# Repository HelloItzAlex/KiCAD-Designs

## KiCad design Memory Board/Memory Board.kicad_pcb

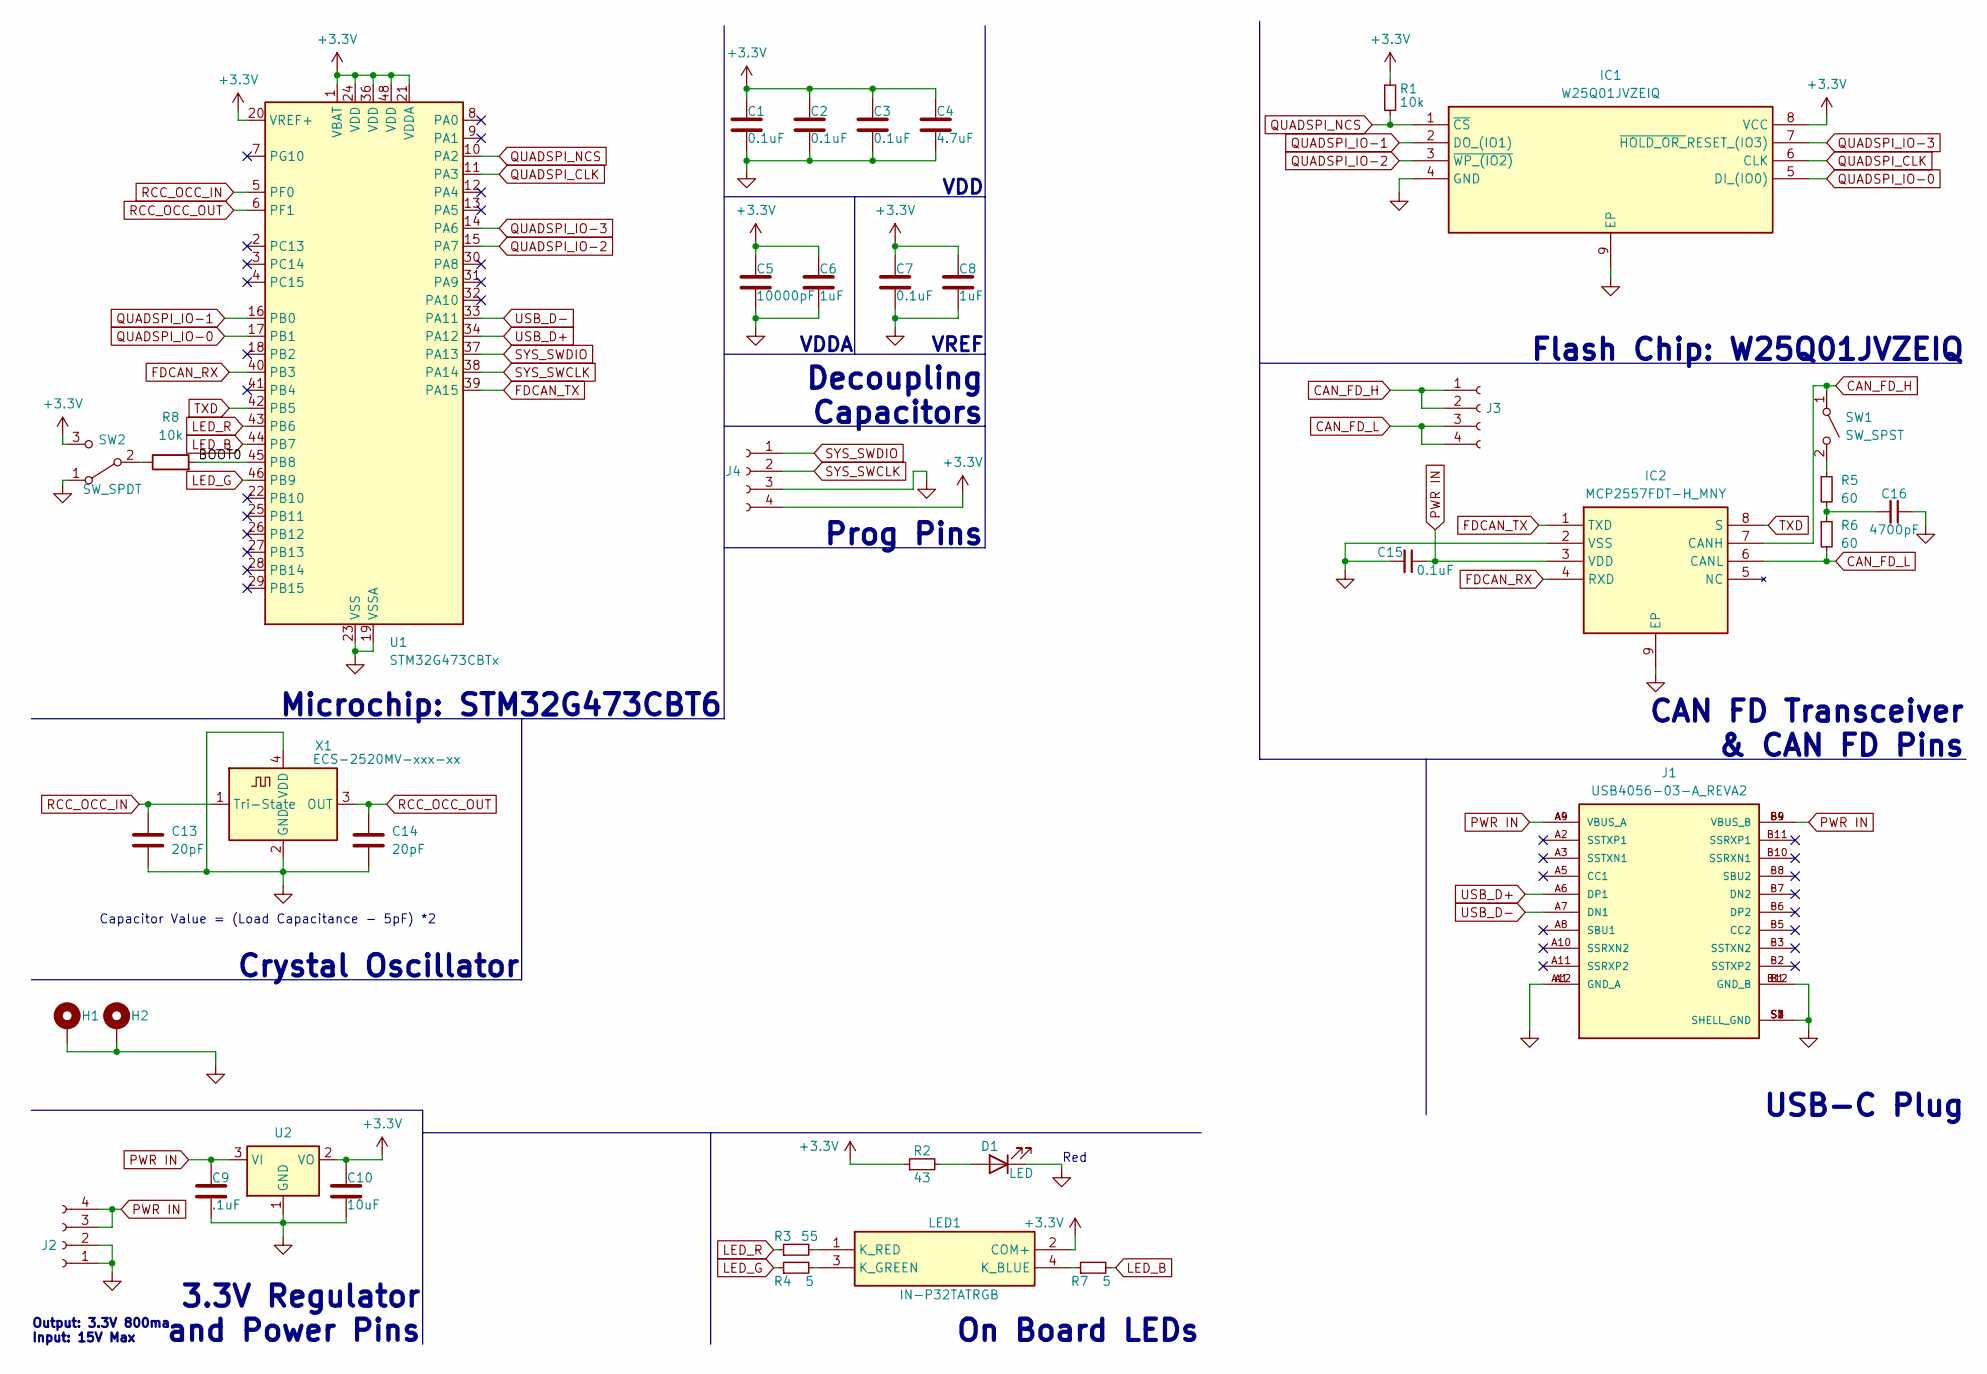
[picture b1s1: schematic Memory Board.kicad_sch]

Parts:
C1, C2, C3, C7, C15: 0.1uF; C_0402_1005Metric
C4: 4.7uF; C_0603_1608Metric
C5: 10000pF; C_0402_1005Metric
C6, C8: 1uF; C_0603_1608Metric
C9: .1uF; C_0402_1005Metric
C10: 10uF; C_0603_1608Metric
C13, C14: 20pF; C_0402_1005Metric
C16: 4700pF; C_0402_1005Metric
D1: LED; LED_0603_1608Metric
H1, H2: MountingHole_Pad; MountingHole_3.2mm_M3_Pad_TopBottom
IC1: W25Q01JVZEIQ; SON127P800X600X80-9N-D; Mouser Part Number 454-W25Q01JVZEIQ
IC2: MCP2557FDT-H_MNY; SON50P300X200X80-9N-D; Mouser Part Number 579-MCP2557FDT-H/MNY
J1: USB4056-03-A_REVA2; USB_C_Receptacle_GCT_USB4115-03-C; PARTREV A2
J2, J3, J4: Conn_01x04_Socket; PinHeader_1x04_P2.54mm_Vertical
LED1: IN-P32TATRGB; INP32TATRGB; Mouser Part Number 743-IN-P32TATRGB
R1: 10k; R_0603_1608Metric
R2: 43; R_0603_1608Metric
R3: 55; R_0402_1005Metric
R4, R7: 5; R_0402_1005Metric
R5, R6: 60; R_0805_2012Metric
R8: 10k; R_0402_1005Metric_Pad0.72x0.64mm_HandSolder
SW1: SW_SPST; SolderJumper-2_P1.3mm_Open_RoundedPad1.0x1.5mm
SW2: SW_SPDT; SolderJumper-3_P1.3mm_Open_RoundedPad1.0x1.5mm_NumberLabels
U1: STM32G473CBTx; LQFP-48_7x7mm_P0.5mm
U2: LD1117S33TR_SOT223; SOT-223-3_TabPin2
X1: ECS-2520MV-xxx-xx; Oscillator_SMD_ECS_2520MV-xxx-xx-4Pin_2.5x2.0mm

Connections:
+3.3V: C1.1, C2.1, C3.1, C4.1, C5.1, C6.1, C7.1, C8.1, C10.1, IC1.8 (VCC), J4.4, LED1.2 (COM+), R1.1, R2.1, SW2.3 (C), U1.1 (VBAT), U1.20 (VREF+), U1.21 (VDDA), U1.24 (VDD), U1.36 (VDD), U1.48 (VDD), U2.2 (VO); also elsewhere on the board
/BOOT0: R8.2, U1.45 (PB8)
CAN_FD_H: IC2.7 (CANH), J3.1, J3.2, SW1.1 (A)
CAN_FD_L: IC2.6 (CANL), J3.3, J3.4, R6.2
FDCAN_RX: IC2.4 (RXD), U1.40 (PB3)
FDCAN_TX: IC2.1 (TXD), U1.39 (PA15)
GND: C1.2, C2.2, C3.2, C4.2, C5.2, C6.2, C7.2, C8.2, C9.2, C10.2, C13.2, C14.2, C15.2, C16.1, D1.1 (K), H1.1, H2.1, IC1.4 (GND), IC1.9 (EP), IC2.2 (VSS), IC2.9 (EP), J1.A1 (GND_A), J1.A12 (GND_A), J1.B1 (GND_B), J1.B12 (GND_B), J1.S1 (SHELL_GND), J1.S2 (SHELL_GND), J1.S3 (SHELL_GND), J1.S4 (SHELL_GND), J2.1, J2.2, J4.3, SW2.1 (A), U1.19 (VSSA), U1.23 (VSS), U1.35 (VSS), U1.47 (VSS), U2.1 (GND), X1.2 (GND), X1.4 (VDD); also elsewhere on the board
LED_B: R7.2, U1.44 (PB7)
LED_G: R4.1, U1.46 (PB9)
LED_R: R3.1, U1.43 (PB6)
unnamed: C16.2, R5.2, R6.1
unnamed: D1.2 (A), R2.2
unnamed: LED1.4 (K_BLUE), R7.1
unnamed: LED1.3 (K_GREEN), R4.2
unnamed: LED1.1 (K_RED), R3.2
unnamed: R5.1, SW1.2 (B)
unnamed: R8.1, SW2.2 (B)
PWR IN: C9.1, C15.1, IC2.3 (VDD), J1.A4 (VBUS_A), J1.A9 (VBUS_A), J1.B4 (VBUS_B), J1.B9 (VBUS_B), J2.3, J2.4, U2.3 (VI)
QUADSPI_CLK: IC1.6 (CLK), U1.11 (PA3); also elsewhere on the board
QUADSPI_IO-0: IC1.5 (DI_(IO0)), U1.17 (PB1); also elsewhere on the board
QUADSPI_IO-1: IC1.2 (DO_(IO1)), U1.16 (PB0); also elsewhere on the board
QUADSPI_IO-2: IC1.3 (~WP_(IO2)), U1.15 (PA7); also elsewhere on the board
QUADSPI_IO-3: IC1.7 (~HOLD_OR_RESET_(IO3)), U1.14 (PA6); also elsewhere on the board
QUADSPI_NCS: IC1.1 (~CS), R1.2, U1.10 (PA2); also elsewhere on the board
RCC_OCC_IN: C13.1, U1.5 (PF0), X1.1 (Tri-State)
RCC_OCC_OUT: C14.1, U1.6 (PF1), X1.3 (OUT)
SYS_SWCLK: J4.2, U1.38 (PA14)
SYS_SWDIO: J4.1, U1.37 (PA13)
TXD: IC2.8 (S), U1.42 (PB5)
USB_D+: J1.A6 (DP1), U1.34 (PA12)
USB_D-: J1.A7 (DN1), U1.33 (PA11)

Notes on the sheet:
Capacitor Value = (Load Capacitance - 5pF) *2
Microchip: STM32G473CBT6
3.3V Regulator and Power Pins
USB-C Plug
Flash Chip: W25Q01JVZEIQ
Crystal Oscillator
On Board LEDs
Output: 3.3V 800ma Input: 15V Max
Red
VDD
CAN FD Transceiver & CAN FD Pins
Decoupling Capacitors
VREF
Prog Pins
VDDA

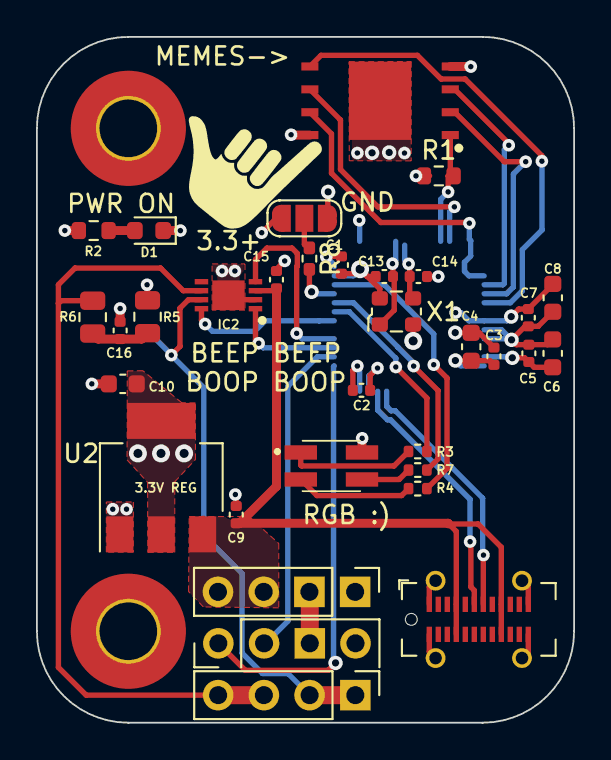
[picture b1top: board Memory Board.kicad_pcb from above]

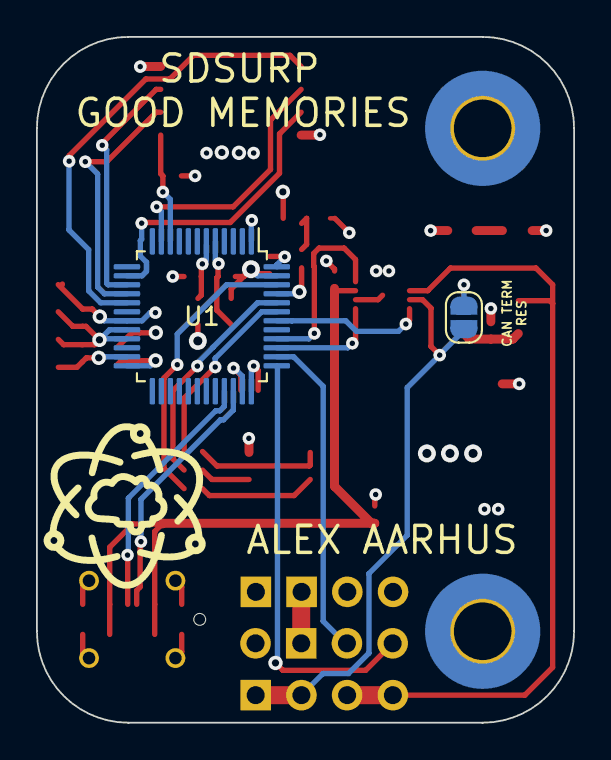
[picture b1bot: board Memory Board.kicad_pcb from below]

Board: 4 copper layers, 29.8 x 38.1 mm, 37 parts (2 on the bottom side), 31 nets.

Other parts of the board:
MEMES->: W25Q01JVZEIQ; SON127P800X600X80-9N-D

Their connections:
+3.3V: MEMES->.8 (VCC); also elsewhere on the board
GND: MEMES->.4 (GND), MEMES->.9 (EP); also elsewhere on the board
QUADSPI_CLK: MEMES->.6 (CLK); also elsewhere on the board
QUADSPI_IO-0: MEMES->.5 (DI_(IO0)); also elsewhere on the board
QUADSPI_IO-1: MEMES->.2 (DO_(IO1)); also elsewhere on the board
QUADSPI_IO-2: MEMES->.3 (~WP_(IO2)); also elsewhere on the board
QUADSPI_IO-3: MEMES->.7 (~HOLD_OR_RESET_(IO3)); also elsewhere on the board
QUADSPI_NCS: MEMES->.1 (~CS); also elsewhere on the board

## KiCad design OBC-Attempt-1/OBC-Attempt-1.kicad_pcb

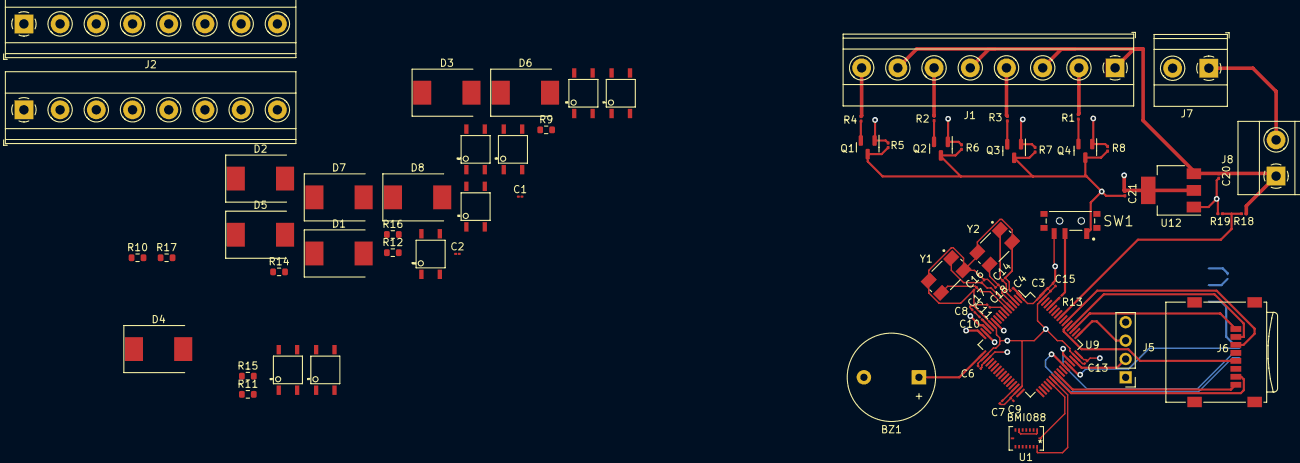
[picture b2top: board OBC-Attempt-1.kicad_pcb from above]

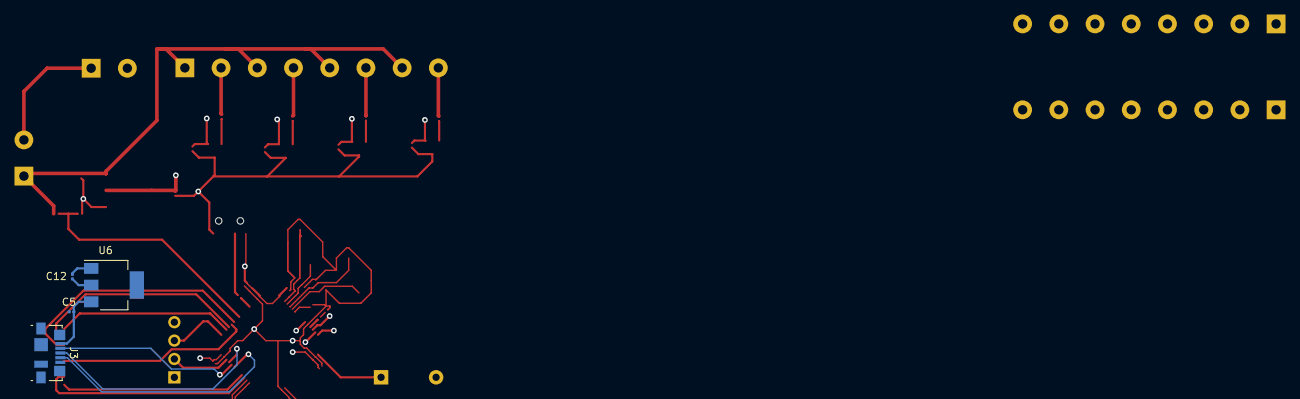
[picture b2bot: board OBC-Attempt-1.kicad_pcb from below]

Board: 4 copper layers, 75 parts (4 on the bottom side), 72 nets.

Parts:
BZ1: Buzzer; Buzzer_12x9.5RM7.6
C1, C2, C3, C4, C6, C8, C9, C11, C13: 100nF; C_01005_0402Metric
C5, C20: 100nF; C_0201_0603Metric
C7, C15: 4.7uF; C_01005_0402Metric
C10: 1uF; C_01005_0402Metric
C12, C21: 10uF; C_0201_0603Metric
C14, C16: 26pf; C_01005_0402Metric
C17, C18: 26uf; C_01005_0402Metric
D1, D2, D3, D4, D5, D6, D7, D8: B330; D_SMC
J1, J2, J4: Screw_Terminal_01x08; TerminalBlock_Phoenix_MKDS-1,5-8_1x08_P5.00mm_Horizontal
J3: USB_B_Micro; USB_Micro-B_Molex_47346-0001
J5: Conn_01x04; PinHeader_1x04_P2.54mm_Vertical
J6: Micro_SD_Card; microSD_HC_Wuerth_693072010801
J7, J8: Screw_Terminal_01x02; TerminalBlock_Phoenix_MKDS-1,5-2_1x02_P5.00mm_Horizontal
Q1, Q2, Q3, Q4: 2N7002K; SOT-23
R1, R2, R3, R4: 1; R_0201_0603Metric
R5, R6, R7, R8: 470; R_0201_0603Metric
R9, R10, R11, R12, R14, R15, R16, R17: 270; R_0603_1608Metric
R13: 10k; R_01005_0402Metric
R18: 1M; R_0201_0603Metric
R19: 100K; R_0201_0603Metric
SW1: PCM12SMTR; SW_PCM12SMTR
U1: BMI088
U2, U3, U4, U5, U7, U8, U10, U11: CPC1020NTR; 4-SOP
U6, U12: NCP1117-3.3_SOT223; SOT-223-3_TabPin2
U9: STM32F401RDTx; LQFP-64_10x10mm_P0.5mm
Y1: ABMM2-25MHZ-D1-T; XTAL_ABMM2-25.000MHZ-D1-T
Y2: ABMM2-32.768MHZ-E2F-T; XTAL_ABMM2-32.768MHZ-E2F-T

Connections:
3.3V: C1.1, C2.1, C3.1, C4.1, C6.1, C9.1, C10.1, C12.1, C13.1, C15.2, C21.1, J5.1, J6.4 (VDD), SW1.3, U1.3 (VDD), U1.11 (VDDIO), U6.2 (VO), U9.1 (VBAT), U9.13 (VREF+), U9.19 (VDD), U9.32 (VDD), U9.48 (VDD), U9.64 (VDD), U12.2 (VO)
BATT+: J7.1, J8.2
BUZZER: BZ1.1 (-), U9.17 (PA3)
CS1_ACC: U1.14 (CSB1), U9.25 (PC5)
CS2_GYRO: U1.5 (CSB2), U9.24 (PC4)
GND: BZ1.2 (+), C1.2, C2.2, C3.2, C4.2, C5.2, C6.2, C7.2, C8.2, C9.2, C11.2, C12.2, C13.2, C14.2, C15.1, C16.2, C17.2, C18.2, C20.2, C21.2, D1.2 (A), D2.2 (A), D3.2 (A), D4.2 (A), D5.2 (A), D6.2 (A), D7.2 (A), D8.2 (A), J2.1, J2.3, J2.5, J2.7, J3.5 (GND), J4.1, J4.3, J4.5, J4.7, J5.4, J6.6 (VSS), J7.2, Q1.3 (D), Q2.3 (D), Q3.3 (D), Q4.3 (D), R5.1, R6.1, R7.1, R8.1, R19.2, SW1.1, U1.2 (NC), U1.4 (GNDA), U1.6 (GNDIO), U1.7 (PS), U2.2, U3.2, U4.2, U5.2, U6.1 (GND), U7.2, U8.2, U9.12 (VSSA), U9.18 (VSS), U9.31 (VSS), U9.47 (VSS), U9.63 (VSS), U10.2, U11.2, U12.1 (GND), Y1.2 (GND), Y1.4 (GND), Y2.2 (GND), Y2.4 (GND)
INT_ACC1: U1.16 (INT1), U9.37 (PC6)
INT_ACC2: U1.1 (INT2), U9.38 (PC7)
INT_GYRO1: U1.12 (INT3), U9.41 (PA8)
INT_GYRO2: U1.13 (INT4), U9.42 (PA9)
MISO: U1.10 (SDO2), U1.15 (SDO1), U9.22 (PA6)
MOSI: U1.9 (SDA/SDI), U9.23 (PA7)
unnamed: C5.1, J3.1 (VBUS), U6.3 (VI)
unnamed: C7.1, U9.30 (VCAP1)
unnamed: C8.1, C10.2
unnamed: C11.1, U9.7 (NRST)
unnamed: D1.1 (K), J2.2, U4.4
unnamed: D2.1 (K), J2.8, U5.4
unnamed: D3.1 (K), J2.4, U2.4
unnamed: D4.1 (K), J2.6, U3.4
unnamed: D5.1 (K), J4.4, U10.4
unnamed: D6.1 (K), J4.6, U11.4
unnamed: D7.1 (K), J4.2, U7.4
unnamed: D8.1 (K), J4.8, U8.4
unnamed: J1.2, R1.2
unnamed: J1.4, R3.2
unnamed: J1.6, R2.2
unnamed: J1.8, R4.2
unnamed: Q1.2 (S), R4.1
unnamed: Q2.2 (S), R2.1
unnamed: Q3.2 (S), R3.1
unnamed: Q4.2 (S), R1.1
unnamed: R9.1, U2.1
unnamed: R10.1, U3.1
unnamed: R11.1, U4.1
unnamed: R12.1, U5.1
unnamed: R13.1, U9.60 (BOOT0)
unnamed: R13.2, SW1.2
unnamed: R14.1, U7.1
unnamed: R15.1, U8.1
unnamed: R16.1, U10.1
unnamed: R17.1, U11.1
PWR: C20.1, J1.1, J1.3, J1.5, J1.7, J8.1, R18.1, U2.3, U3.3, U4.3, U5.3, U7.3, U8.3, U10.3, U11.3, U12.3 (VI)
PYRO1: Q4.1 (G), R8.2, U9.11 (PC3)
PYRO2: Q3.1 (G), R7.2, U9.14 (PA0)
PYRO3: Q2.1 (G), R6.2, U9.15 (PA1)
PYRO4: Q1.1 (G), R5.2, U9.16 (PA2)
RCC_OSC32_IN: C14.1, U9.3 (PC14), Y2.1
RCC_OSC32_OUT: C18.1, U9.4 (PC15), Y2.3
RCC_OSC_IN: C16.1, U9.5 (PH0), Y1.1
RCC_OSC_OUT: C17.1, U9.6 (PH1), Y1.3
SCK: U1.8 (SCL/SCK), U9.21 (PA5)
SDIO_CK: J6.5 (CLK), U9.53 (PC12)
SDIO_CMD: J6.3 (CMD), U9.54 (PD2)
SDIO_D0: J6.7 (DAT0), U9.39 (PC8)
SDIO_D1: J6.8 (DAT1), U9.40 (PC9)
SDIO_D2: J6.1 (DAT2), U9.51 (PC10)
SDIO_D3: J6.2 (DAT3/CD), U9.52 (PC11)
SOL1: R11.2, U9.26 (PB0)
SOL2: R9.2, U9.27 (PB1)
SOL3: R10.2, U9.28 (PB2)
SOL4: R12.2, U9.29 (PB10)
SOL5: R14.2, U9.33 (PB12)
SOL6: R16.2, U9.34 (PB13)
SOL7: R17.2, U9.35 (PB14)
SOL8: R15.2, U9.36 (PB15)
SYS_JTCK_SWCLK: J5.3, U9.49 (PA14)
SYS_JTMS-SWDIO: J5.2, U9.46 (PA13)
USB_OTG_FS_DM: J3.2 (D-), U9.44 (PA11)
USB_OTG_FS_DP: J3.3 (D+), U9.45 (PA12)
USB_OTG_FS_ID: J3.4 (ID), U9.43 (PA10)
VMON: R18.2, R19.1, U9.56 (PB4)

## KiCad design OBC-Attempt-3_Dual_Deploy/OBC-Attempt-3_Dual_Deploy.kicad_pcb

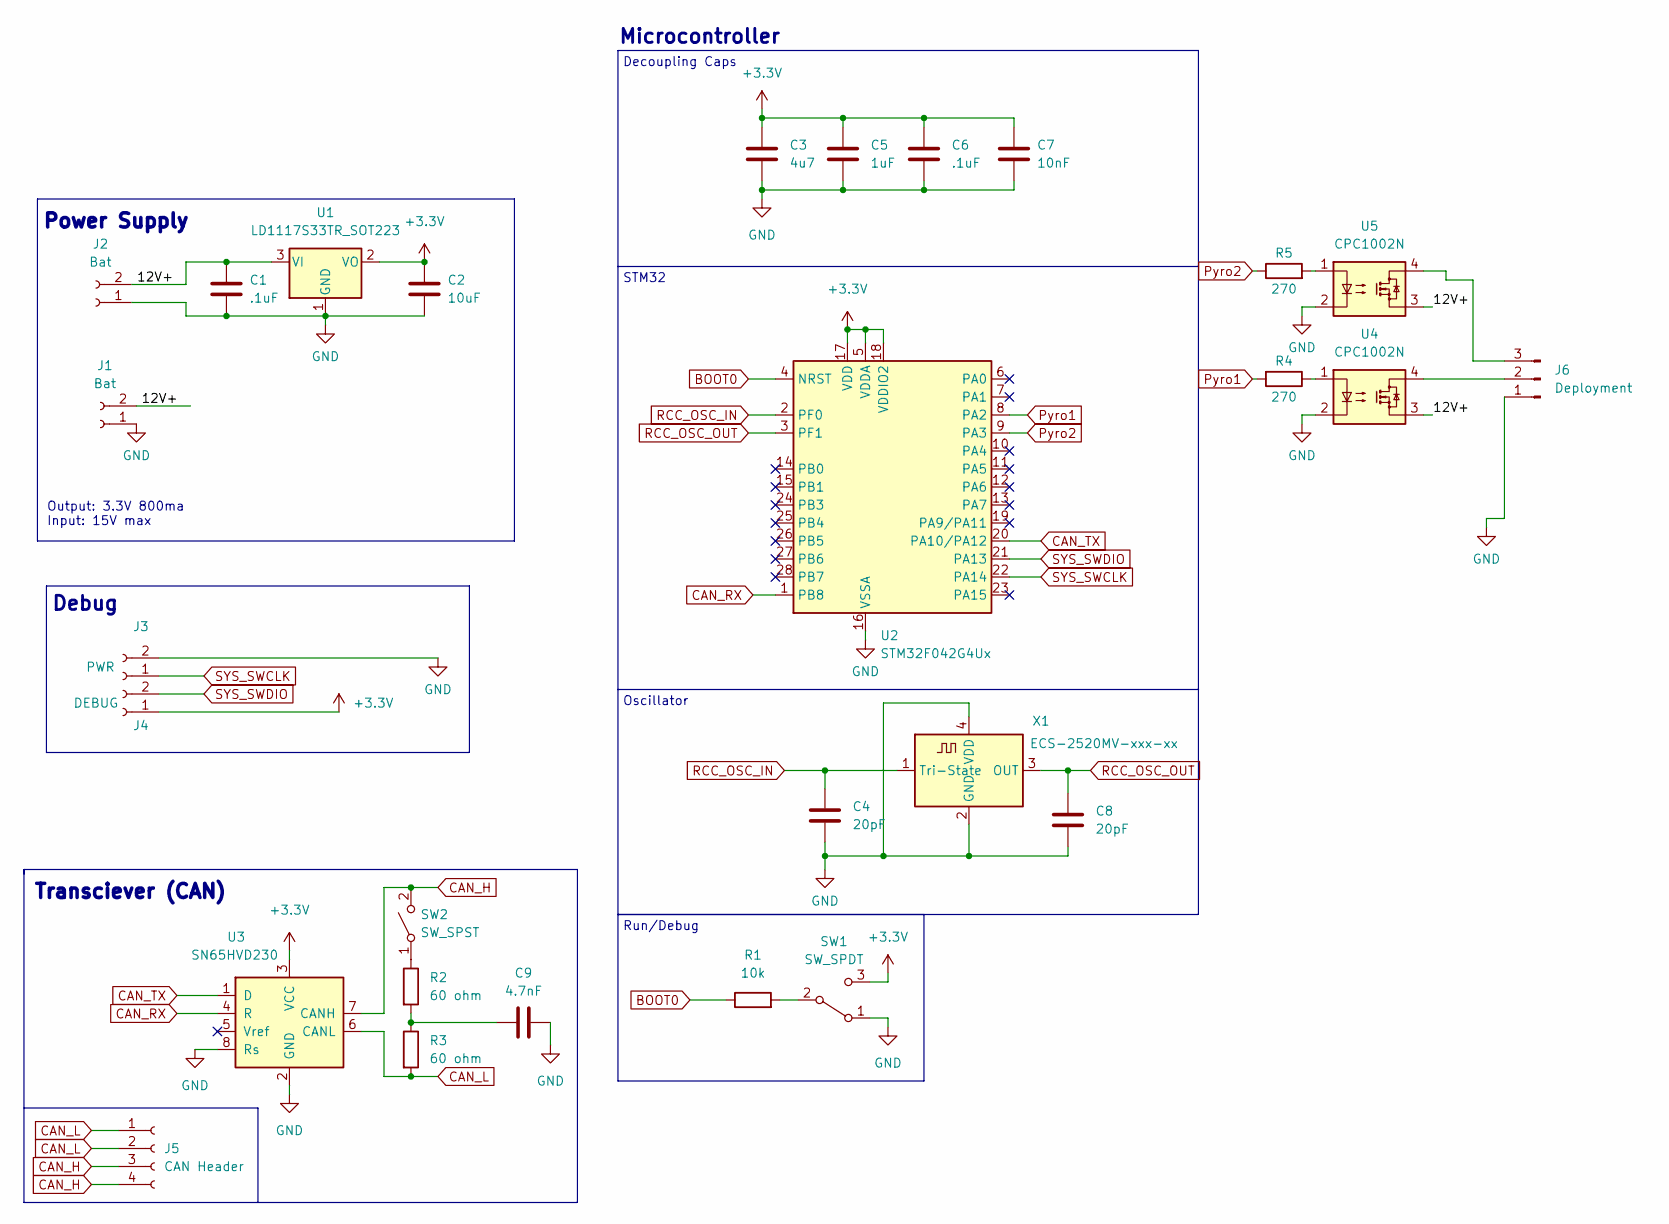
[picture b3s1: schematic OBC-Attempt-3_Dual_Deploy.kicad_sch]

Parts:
C1, C6: .1uF; C_0402_1005Metric
C2: 10uF; C_0603_1608Metric
C3: 4u7; C_0402_1005Metric
C4, C8: 20pF; C_0402_1005Metric
C5: 1uF; C_0402_1005Metric
C7: 10nF; C_0402_1005Metric
C9: 4.7nF; C_0402_1005Metric
J1, J2: Bat; PinHeader_1x02_P1.00mm_Vertical
J3: PWR; PinHeader_1x02_P1.00mm_Vertical
J4: DEBUG; PinHeader_1x02_P1.00mm_Vertical
J5: CAN Header; PinHeader_1x04_P1.00mm_Vertical
J6: Deployment; PinSocket_1x03_P2.54mm_Vertical
R1: 10k; R_0402_1005Metric
R2, R3: 60 ohm; R_0805_2012Metric
R4, R5: 270; R_0402_1005Metric
SW1: SW_SPDT; SolderJumper-3_P1.3mm_Open_RoundedPad1.0x1.5mm_NumberLabels
SW2: SW_SPST; SolderJumper-2_P1.3mm_Open_RoundedPad1.0x1.5mm
U1: LD1117S33TR_SOT223; SOT-223-3_TabPin2
U2: STM32F042G4Ux; QFN-28_4x4mm_P0.5mm
U3: SN65HVD230; SOIC-8_3.9x4.9mm_P1.27mm
U4, U5: CPC1002N; SOP-4_3.8x4.1mm_P2.54mm
X1: ECS-2520MV-xxx-xx; Oscillator_SMD_ECS_2520MV-xxx-xx-4Pin_2.5x2.0mm

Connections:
+3.3V: C2.1, C3.1, C5.1, C6.1, C7.1, J4.1, SW1.3 (C), U1.2 (VO), U2.5 (VDDA), U2.17 (VDD), U2.18 (VDDIO2), U3.3 (VCC)
/12V+: C1.1, J1.2, J2.2, U1.3 (VI), U4.3, U5.3
BOOT0: R1.1, U2.4 (NRST)
CAN_H: J5.3, J5.4, SW2.2 (B), U3.7 (CANH)
CAN_L: J5.1, J5.2, R3.2, U3.6 (CANL)
CAN_RX: U2.1 (PB8), U3.4 (R)
CAN_TX: U2.20 (PA10/PA12), U3.1 (D)
GND: C1.2, C2.2, C3.2, C4.2, C5.2, C6.2, C7.2, C8.2, C9.2, J1.1, J2.1, J3.2, J6.1, SW1.1 (A), U1.1 (GND), U2.16 (VSSA), U3.2 (GND), U3.8 (Rs), U4.2, U5.2, X1.2 (GND), X1.4 (VDD)
unnamed: C9.1, R2.2, R3.1
unnamed: R1.2, SW1.2 (B)
unnamed: R2.1, SW2.1 (A)
unnamed: R4.1, U4.1
unnamed: R5.2, U5.1
unnamed: J6.2, U4.4
unnamed: J6.3, U5.4
Pyro1: R4.2, U2.8 (PA2)
Pyro2: R5.1, U2.9 (PA3)
RCC_OSC_IN: C4.1, U2.2 (PF0), X1.1 (Tri-State)
RCC_OSC_OUT: C8.1, U2.3 (PF1), X1.3 (OUT)
SYS_SWCLK: J3.1, U2.22 (PA14)
SYS_SWDIO: J4.2, U2.21 (PA13)

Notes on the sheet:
Debug
Microcontroller
Output: 3.3V 800ma Input: 15V max
Oscillator
Run/Debug
Power Supply
Decoupling Caps
Transciever (CAN)
STM32

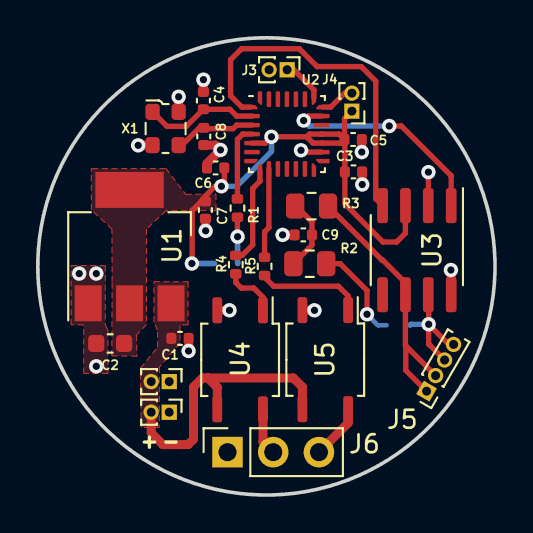
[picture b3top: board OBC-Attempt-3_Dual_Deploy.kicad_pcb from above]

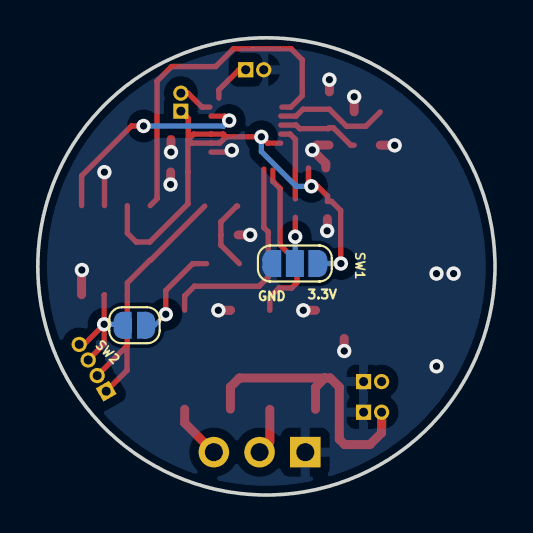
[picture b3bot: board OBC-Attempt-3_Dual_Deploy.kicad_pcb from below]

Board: 2 copper layers, 25.4 x 25.4 mm, 28 parts (2 on the bottom side), 21 nets.

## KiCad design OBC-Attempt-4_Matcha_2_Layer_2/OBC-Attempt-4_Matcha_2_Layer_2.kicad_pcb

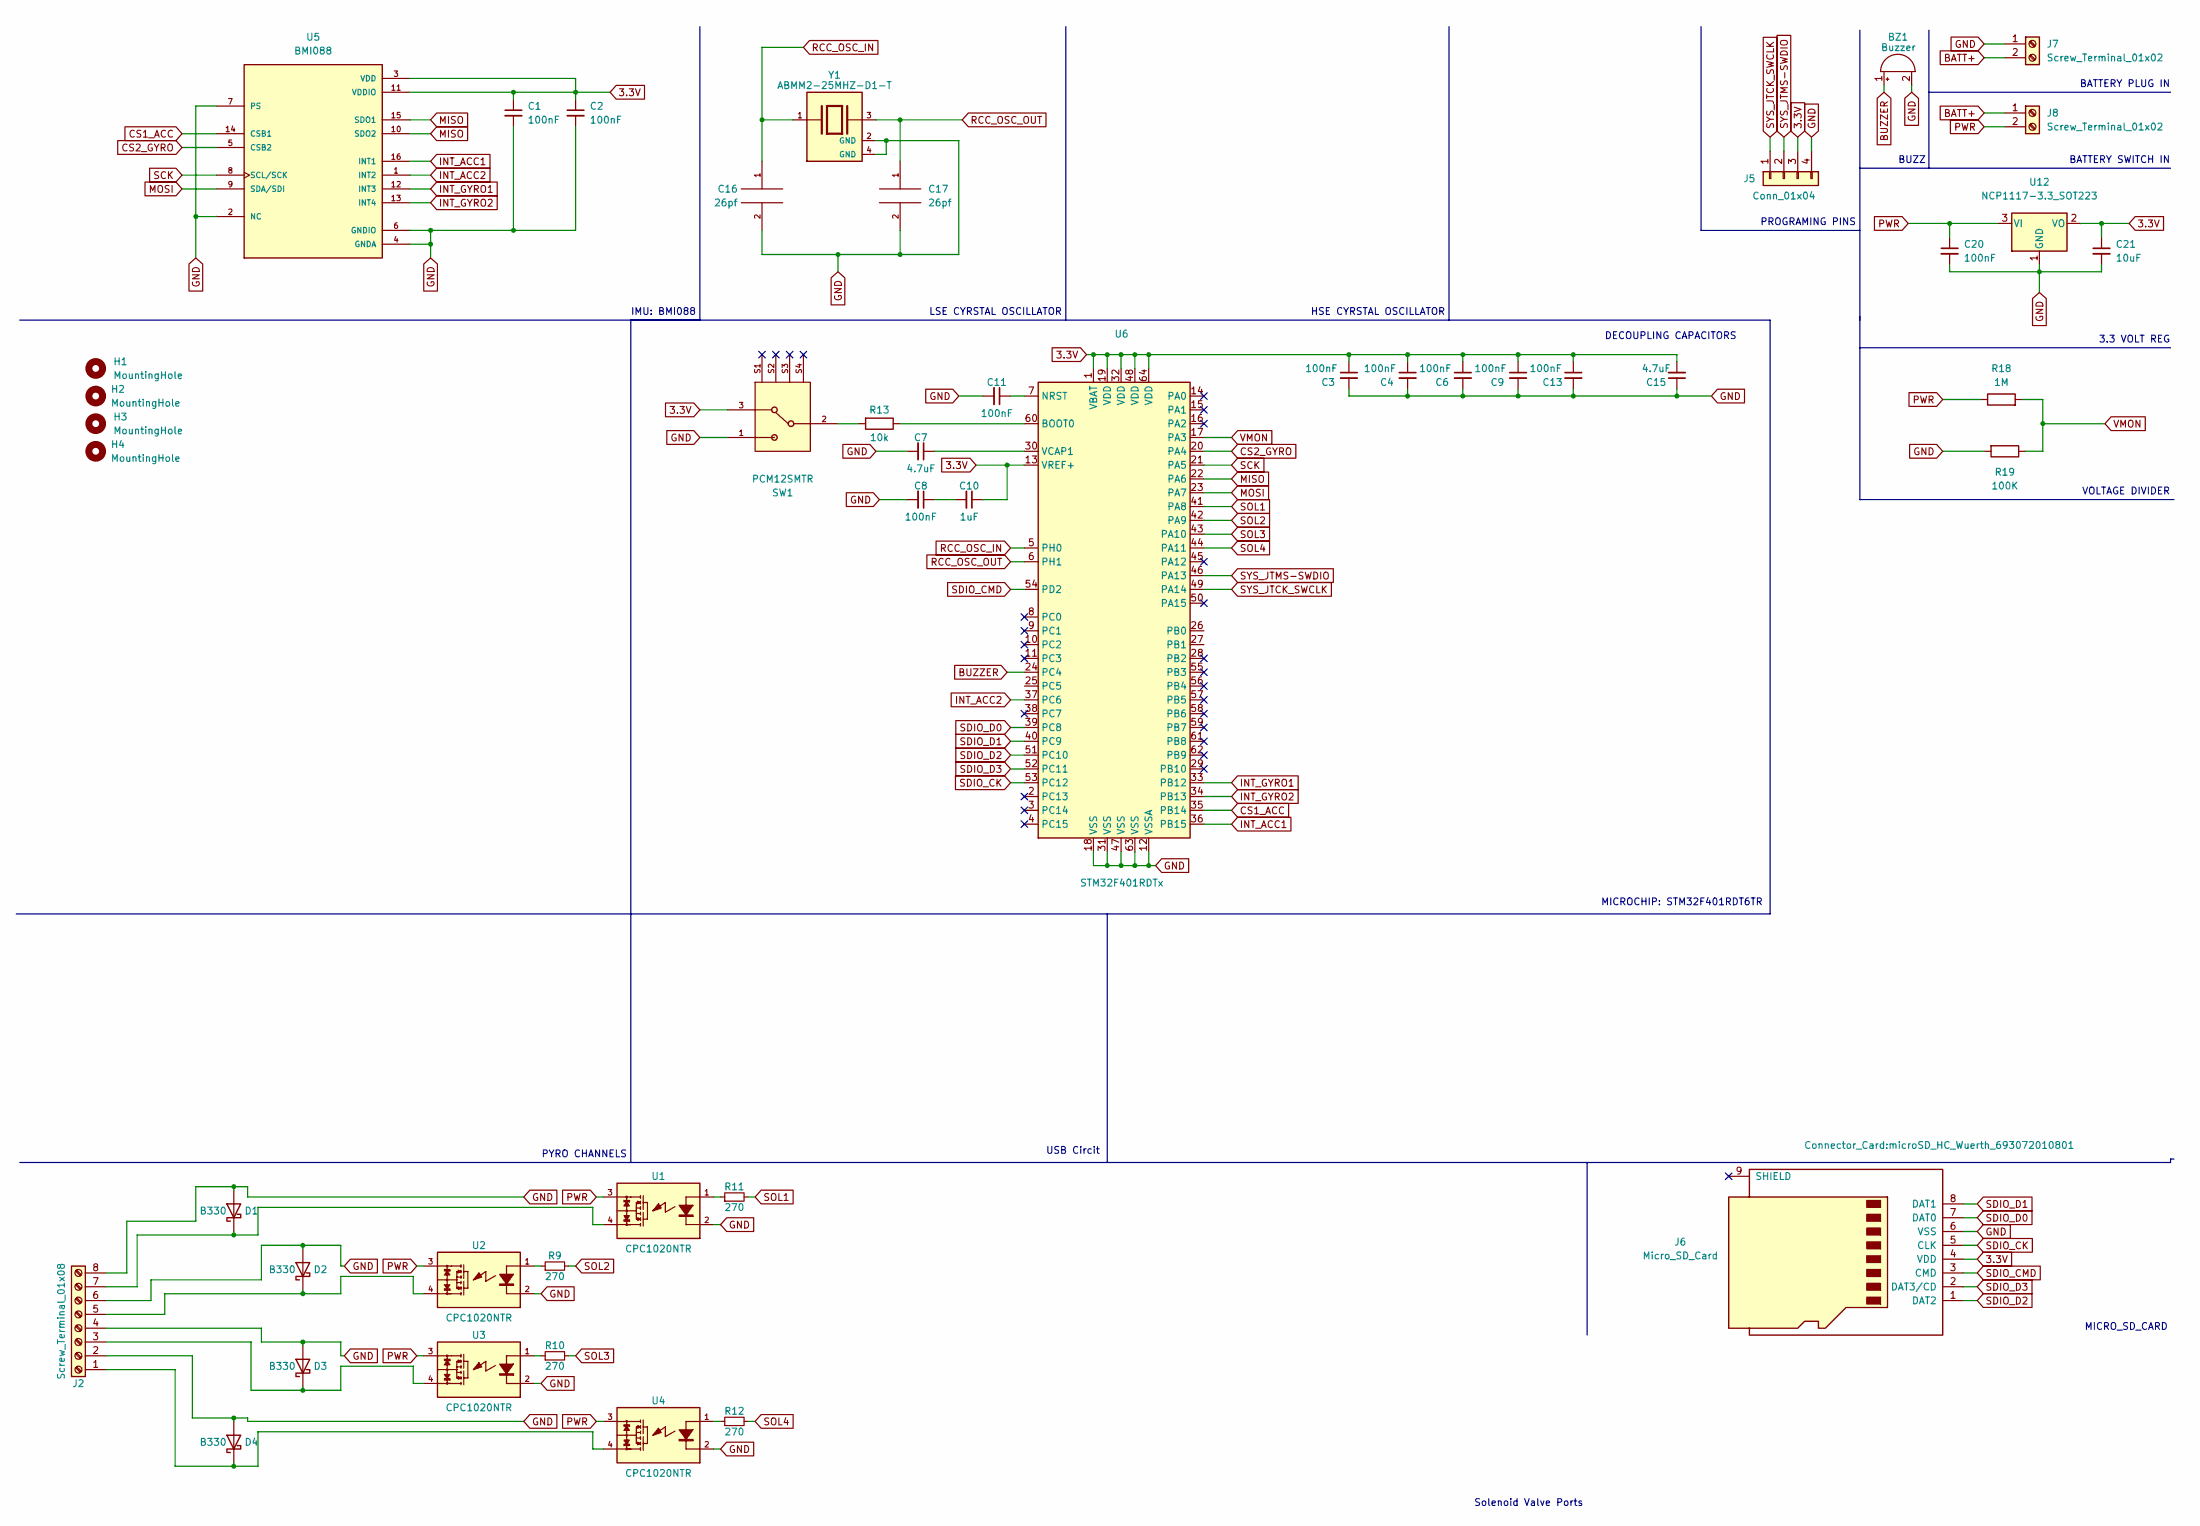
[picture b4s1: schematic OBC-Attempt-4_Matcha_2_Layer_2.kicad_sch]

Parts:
BZ1: Buzzer; Buzzer_TDK_PS1240P02BT_D12.2mm_H6.5mm
C1, C2, C3, C4, C6, C8, C9, C11, C13: 100nF; C_0402_1005Metric
C7: 4.7uF; C_0402_1005Metric
C10: 1uF; C_0603_1608Metric
C15: 4.7uF; C_0603_1608Metric
C16, C17: 26pf; C_0402_1005Metric
C20: 100nF; C_0603_1608Metric
C21: 10uF; C_0603_1608Metric
D1, D2, D3, D4: B330; D_SMA
H1, H2, H3, H4: MountingHole; MountingHole_3mm
J2: Screw_Terminal_01x08; TerminalBlock_Phoenix_MPT-0,5-8-2.54_1x08_P2.54mm_Horizontal
J5: Conn_01x04; PinHeader_1x04_P2.54mm_Vertical
J6: Micro_SD_Card; microSD_HC_Wuerth_693072010801
J7, J8: Screw_Terminal_01x02; TerminalBlock_Phoenix_MPT-0,5-2-2.54_1x02_P2.54mm_Horizontal
R9, R10, R11, R12: 270; R_0603_1608Metric
R13: 10k; R_0603_1608Metric
R18: 1M; R_0603_1608Metric
R19: 100K; R_0603_1608Metric
SW1: PCM12SMTR; SW_PCM12SMTR
U1, U2, U3, U4: CPC1020NTR; 4-SOP
U5: BMI088
U6: STM32F401RDTx; LQFP-64_10x10mm_P0.5mm
U12: NCP1117-3.3_SOT223; SOT-223-3_TabPin2
Y1: ABMM2-25MHZ-D1-T; XTAL_ABMM2-25.000MHZ-D1-T; PARTREV 01.18.13

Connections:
3.3V: C1.1, C2.1, C3.1, C4.1, C6.1, C9.1, C10.1, C13.1, C15.2, C21.1, J5.3, J6.4 (VDD), SW1.3, U5.3 (VDD), U5.11 (VDDIO), U6.1 (VBAT), U6.13 (VREF+), U6.19 (VDD), U6.32 (VDD), U6.48 (VDD), U6.64 (VDD), U12.2 (VO)
BATT+: J7.2, J8.1
BUZZER: BZ1.1 (-), U6.24 (PC4)
CS1_ACC: U5.14 (CSB1), U6.35 (PB14)
CS2_GYRO: U5.5 (CSB2), U6.20 (PA4)
GND: BZ1.2 (+), C1.2, C2.2, C3.2, C4.2, C6.2, C7.2, C8.2, C9.2, C11.2, C13.2, C15.1, C16.2, C17.2, C20.2, C21.2, D1.2 (A), D2.2 (A), D3.2 (A), D4.2 (A), J2.2, J2.4, J2.6, J2.8, J5.4, J6.6 (VSS), J7.1, R19.2, SW1.1, U1.2, U2.2, U3.2, U4.2, U5.2 (NC), U5.4 (GNDA), U5.6 (GNDIO), U5.7 (PS), U6.12 (VSSA), U6.18 (VSS), U6.31 (VSS), U6.47 (VSS), U6.63 (VSS), U12.1 (GND), Y1.2 (GND), Y1.4 (GND)
INT_ACC1: U5.16 (INT1), U6.36 (PB15)
INT_ACC2: U5.1 (INT2), U6.37 (PC6)
INT_GYRO1: U5.12 (INT3), U6.33 (PB12)
INT_GYRO2: U5.13 (INT4), U6.34 (PB13)
MISO: U5.10 (SDO2), U5.15 (SDO1), U6.22 (PA6)
MOSI: U5.9 (SDA/SDI), U6.23 (PA7)
unnamed: C7.1, U6.30 (VCAP1)
unnamed: C8.1, C10.2
unnamed: C11.1, U6.7 (NRST)
unnamed: D1.1 (K), J2.7, U1.4
unnamed: D2.1 (K), J2.5, U2.4
unnamed: D3.1 (K), J2.3, U3.4
unnamed: D4.1 (K), J2.1, U4.4
unnamed: R9.1, U2.1
unnamed: R10.1, U3.1
unnamed: R11.1, U1.1
unnamed: R12.1, U4.1
unnamed: R13.1, U6.60 (BOOT0)
unnamed: R13.2, SW1.2
PWR: C20.1, J8.2, R18.1, U1.3, U2.3, U3.3, U4.3, U12.3 (VI)
RCC_OSC_IN: C16.1, U6.5 (PH0), Y1.1
RCC_OSC_OUT: C17.1, U6.6 (PH1), Y1.3
SCK: U5.8 (SCL/SCK), U6.21 (PA5)
SDIO_CK: J6.5 (CLK), U6.53 (PC12)
SDIO_CMD: J6.3 (CMD), U6.54 (PD2)
SDIO_D0: J6.7 (DAT0), U6.39 (PC8)
SDIO_D1: J6.8 (DAT1), U6.40 (PC9)
SDIO_D2: J6.1 (DAT2), U6.51 (PC10)
SDIO_D3: J6.2 (DAT3/CD), U6.52 (PC11)
SOL1: R11.2, U6.41 (PA8)
SOL2: R9.2, U6.42 (PA9)
SOL3: R10.2, U6.43 (PA10)
SOL4: R12.2, U6.44 (PA11)
SYS_JTCK_SWCLK: J5.1, U6.49 (PA14)
SYS_JTMS-SWDIO: J5.2, U6.46 (PA13)
VMON: R18.2, R19.1, U6.17 (PA3)

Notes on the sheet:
DECOUPLING CAPACITORS
IMU: BMI088
3.3 VOLT REG
LSE CYRSTAL OSCILLATOR
PROGRAMING PINS
HSE CYRSTAL OSCILLATOR
MICRO_SD_CARD
MICROCHIP: STM32F401RDT6TR
VOLTAGE DIVIDER
BATTERY PLUG IN
BUZZ
Solenoid Valve Ports
USB Circit
PYRO CHANNELS
BATTERY SWITCH IN

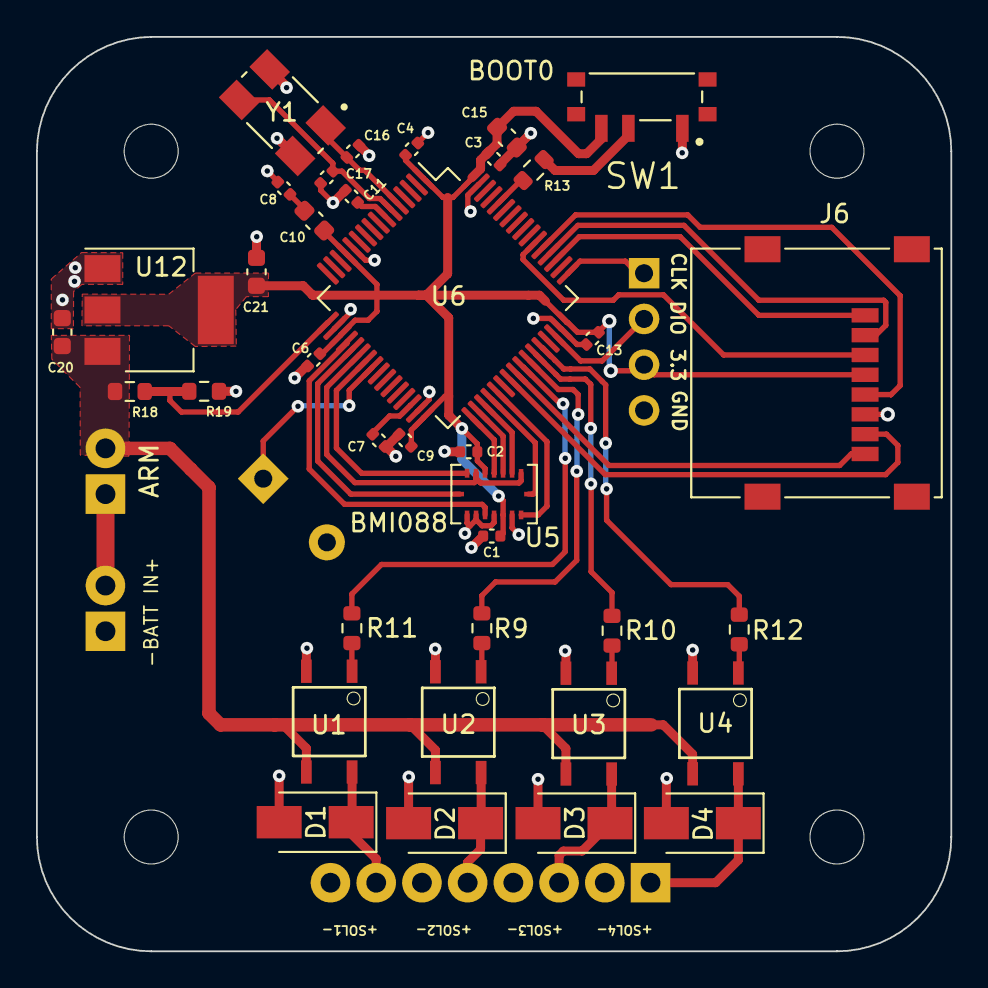
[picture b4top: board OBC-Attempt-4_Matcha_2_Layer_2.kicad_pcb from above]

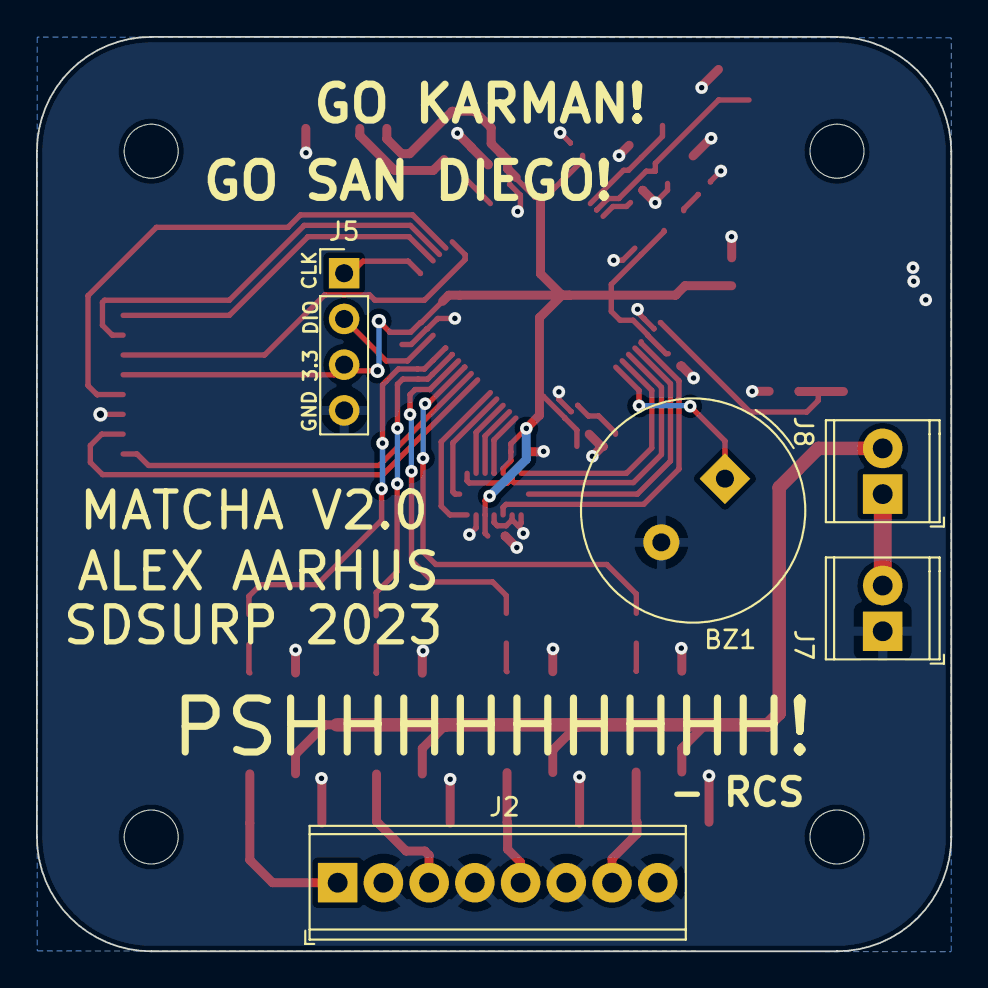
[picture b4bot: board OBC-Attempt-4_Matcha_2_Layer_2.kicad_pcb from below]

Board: 2 copper layers, 50.8 x 50.8 mm, 46 parts (5 on the bottom side), 42 nets.

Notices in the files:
parts and their libraries:
Copyright 2021 Accelerated Designs. All rights reserved.
